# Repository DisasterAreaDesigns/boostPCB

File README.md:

# boostPCB

Documentation for the Disaster Area Designs DIY Boost Kit PCB

.sch and .brd are EAGLE CAD files

gerbers folder has 274-X gerber files for making your own boards at commercial PCB fabs

BOM and schematic in PDF format

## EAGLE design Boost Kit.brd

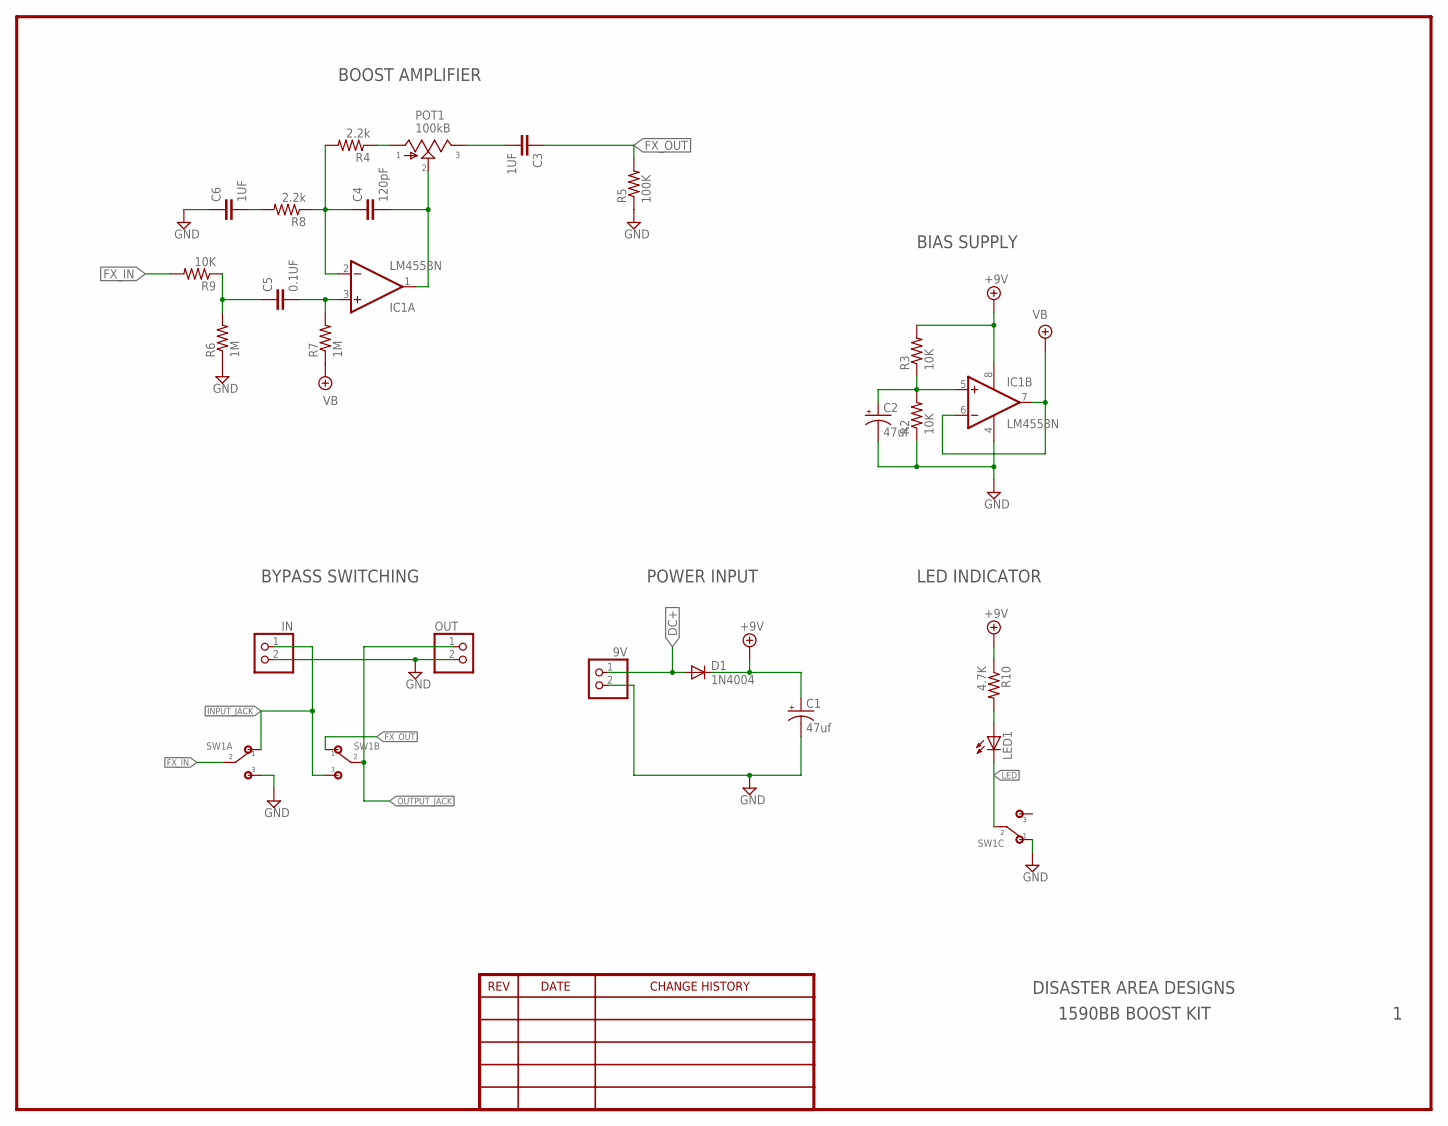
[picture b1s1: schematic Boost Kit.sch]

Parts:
9V: PINHD-1X2; 1X02
C1, C2: 47uf; E2,5-6
C3, C6: 1UF; 072X035
C4: 120pF; 072X035
C5: 0.1UF; 072X035
D1: 1N4004; DO41-10
IC1: LM4558N; DIL08
IN: PINHD-1X2; 1X02
LED1: LED5MM
OUT: PINHD-1X2; 1X02
POT1: 100kB; 16MM
R2, R3, R9: 10K; R0207/4
R4, R8: 2.2k; R0207/4
R5: 100K; R0207/4
R6, R7: 1M; R0207/4
R10: 4.7K; R0207/4
SW1: 3PDT

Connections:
+9V: C1.+, D1.C, IC1.8 (V+), R3.2, R10.1
DC+: 9V.1, D1.A
FX_IN: R9.2, SW1.A2
FX_IN2: C5.1, R6.2, R9.1
FX_OUT: C3.1, R5.2, SW1.B1
GND: 9V.2, C1.-, C2.-, C6.1, IC1.4 (V-), IN.2, OUT.2, R2.1, R5.1, R6.1, SW1.A3, SW1.C1
INPUT_JACK: IN.1, SW1.A1, SW1.B3
LED: LED1.K (C), SW1.C2
unnamed: LED1.A, R10.2
unnamed: C4.2, IC1.1 (OUT), POT1.2
unnamed: C4.1, IC1.2 (-IN), R4.2, R8.1
unnamed: C6.2, R8.2
unnamed: POT1.1, R4.1
unnamed: C2.+, IC1.5 (+IN), R2.2, R3.1
unnamed: C3.2, POT1.3
unnamed: C5.2, IC1.3 (+IN), R7.2
OUTPUT_JACK: OUT.1, SW1.B2
VB: IC1.6 (-IN), IC1.7 (OUT), R7.1

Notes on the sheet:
1590BB BOOST KIT
DISASTER AREA DESIGNS
BOOST AMPLIFIER
BIAS SUPPLY
BYPASS SWITCHING
POWER INPUT
LED INDICATOR

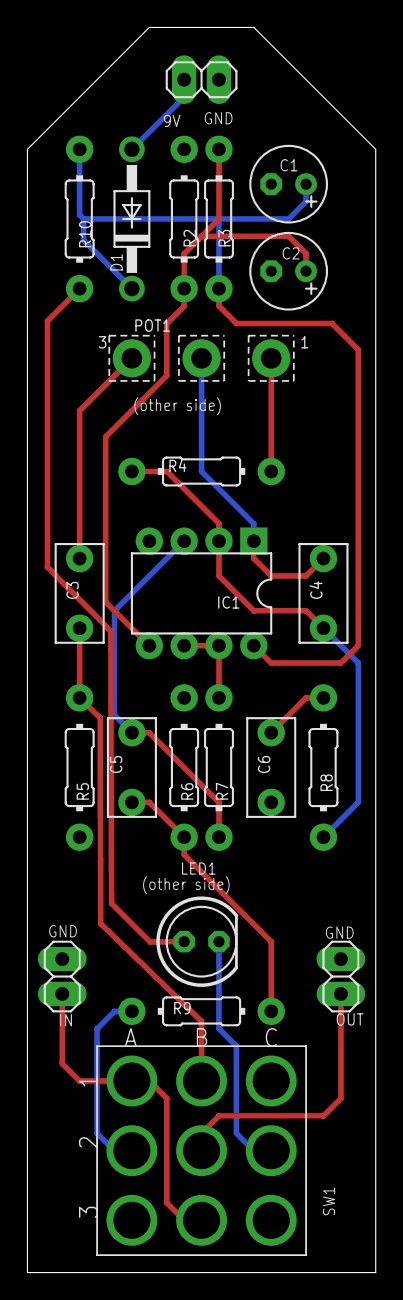
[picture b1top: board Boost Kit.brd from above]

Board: 2 copper layers, 25.4 x 90.8 mm, 23 parts (0 on the bottom side), 18 nets.

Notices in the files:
parts and their libraries:
apex-dframes: Copyright (C) 2004, Bob Starr (bobstarr@mindspring.com)
